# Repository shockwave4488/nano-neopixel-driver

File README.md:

# Nano NeoPixel driver
An all in one board for driving neopixel, or equivalent, led strips using an Arduino Nano

**WARNING: THIS BOARD IS 5V ONLY. APPLYING A HIGHER VOLTAGE WILL RESULT IN A DEAD ARDUINO AND LEDS**

Instructions for the jumpers on the back <br>
Adafruit recommends putting a 470 ohm resistor in series with the WS2812B data line. To acomodate both LED and GPIO signals, the back of the board has a resistor footprint and a solder jumper for each exposed DIO. Populate the resistor for DIO that will drive an LED signal, and solder the jumper for DIO that will be GPIO.

Assembly
1) Populatate the resistors and jumpers on the back as needed
2) Install the arduino
3) Attach wire or headers for Vin and the DIO
4) Install the capacitor

BOM <br>
1x Arduino Nano <br>
1x 1000uF Würth Elektronik 860010274015 (or comparable capacitor with same footprint) <br>
8x 470 ohm 0805 resistors <br>

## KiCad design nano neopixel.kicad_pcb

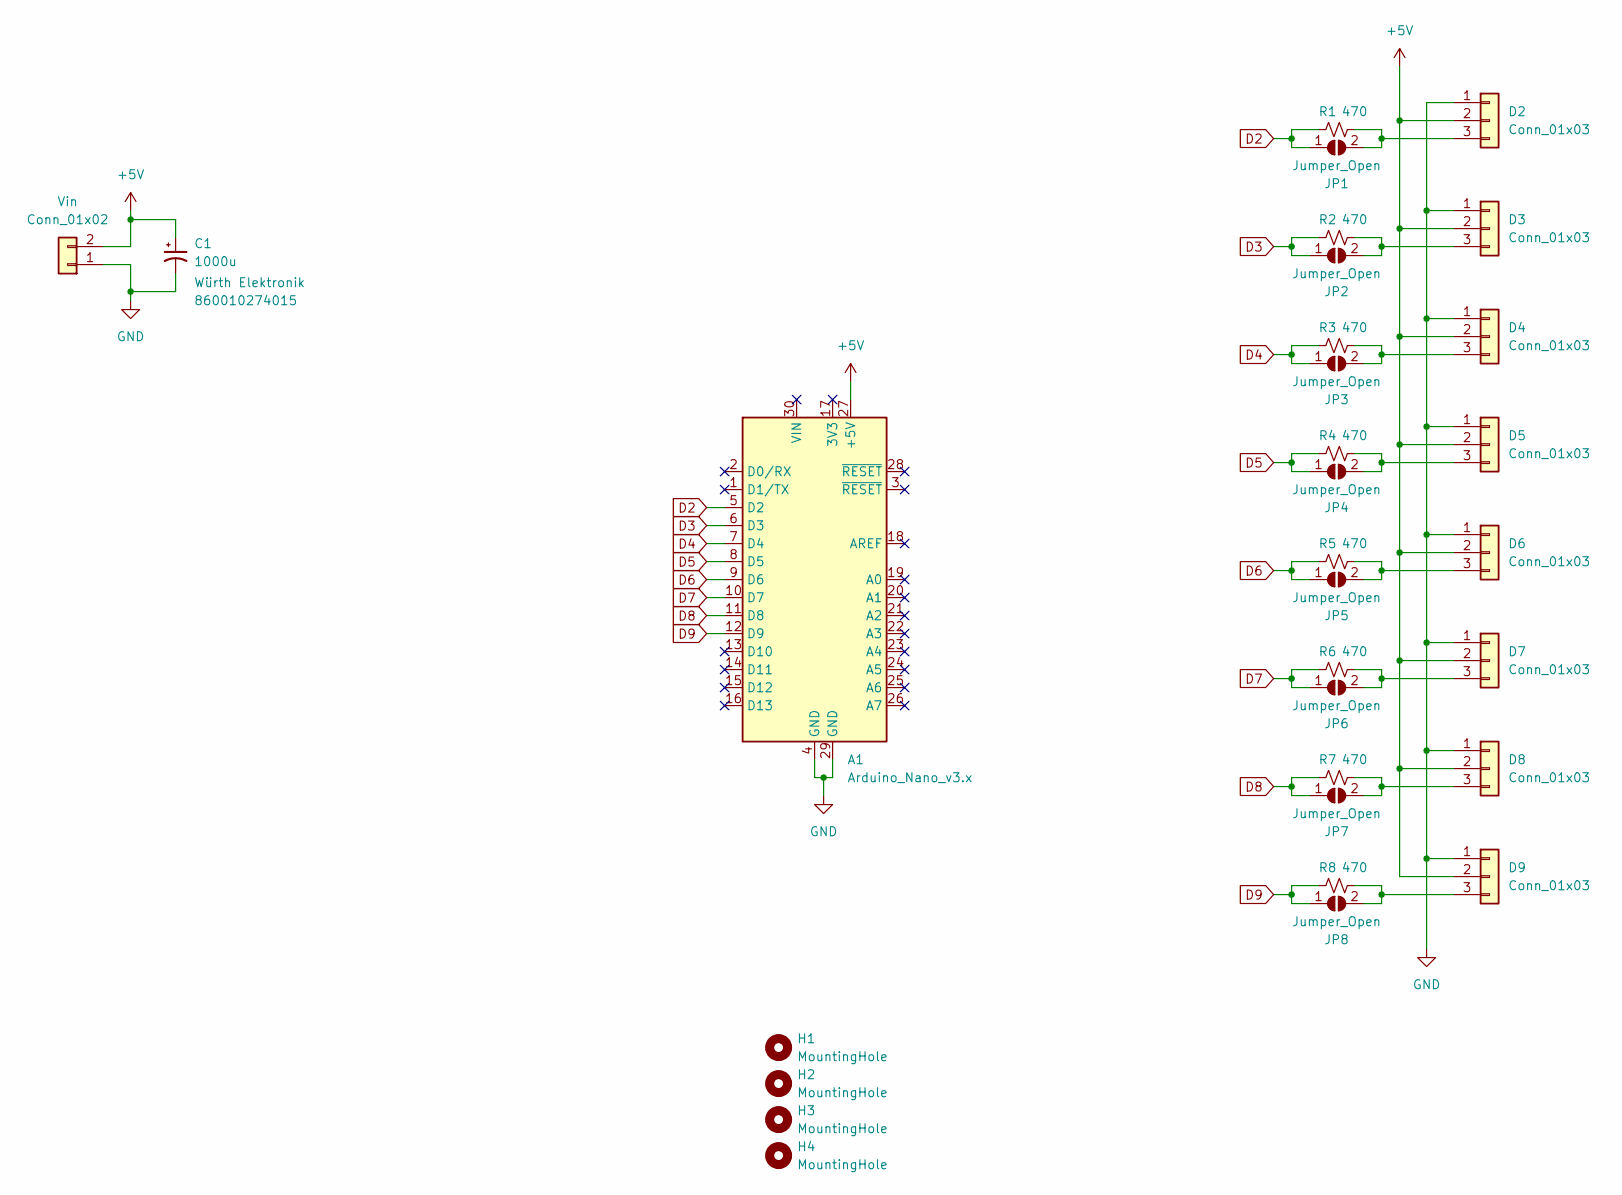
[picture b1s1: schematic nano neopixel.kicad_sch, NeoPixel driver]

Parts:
A1: Arduino_Nano_v3.x; Arduino_Nano
C1: 1000u; CP_Radial_D8.0mm_P3.50mm
D2, D3, D4, D5, D6, D7, D8, D9: Conn_01x03; PinHeader_1x03_P2.54mm_Vertical
H1, H2, H3, H4: MountingHole; MountingHole_3.2mm_M3
JP1, JP2, JP3, JP4, JP5, JP6, JP7, JP8: Jumper_Open; SolderJumper-2_P1.3mm_Open_Pad1.0x1.5mm
R1, R2, R3, R4, R5, R6, R7, R8: 470; R_0805_2012Metric
Vin: Conn_01x02; PinHeader_1x02_P2.54mm_Vertical

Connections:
+5V: A1.27 (+5V), C1.1, D2.2, D3.2, D4.2, D5.2, D6.2, D7.2, D8.2, D9.2, Vin.2
D2: A1.5 (D2), JP1.1 (A), R1.1
D3: A1.6 (D3), JP2.1 (A), R2.1
D4: A1.7 (D4), JP3.1 (A), R3.1
D5: A1.8 (D5), JP4.1 (A), R4.1
D6: A1.9 (D6), JP5.1 (A), R5.1
D7: A1.10 (D7), JP6.1 (A), R6.1
D8: A1.11 (D8), JP7.1 (A), R7.1
D9: A1.12 (D9), JP8.1 (A), R8.1
GND: A1.4 (GND), A1.29 (GND), C1.2, D2.1, D3.1, D4.1, D5.1, D6.1, D7.1, D8.1, D9.1, Vin.1
unnamed: D2.3, JP1.2 (B), R1.2
unnamed: D3.3, JP2.2 (B), R2.2
unnamed: D4.3, JP3.2 (B), R3.2
unnamed: D5.3, JP4.2 (B), R4.2
unnamed: D6.3, JP5.2 (B), R5.2
unnamed: D7.3, JP6.2 (B), R6.2
unnamed: D8.3, JP7.2 (B), R7.2
unnamed: D9.3, JP8.2 (B), R8.2

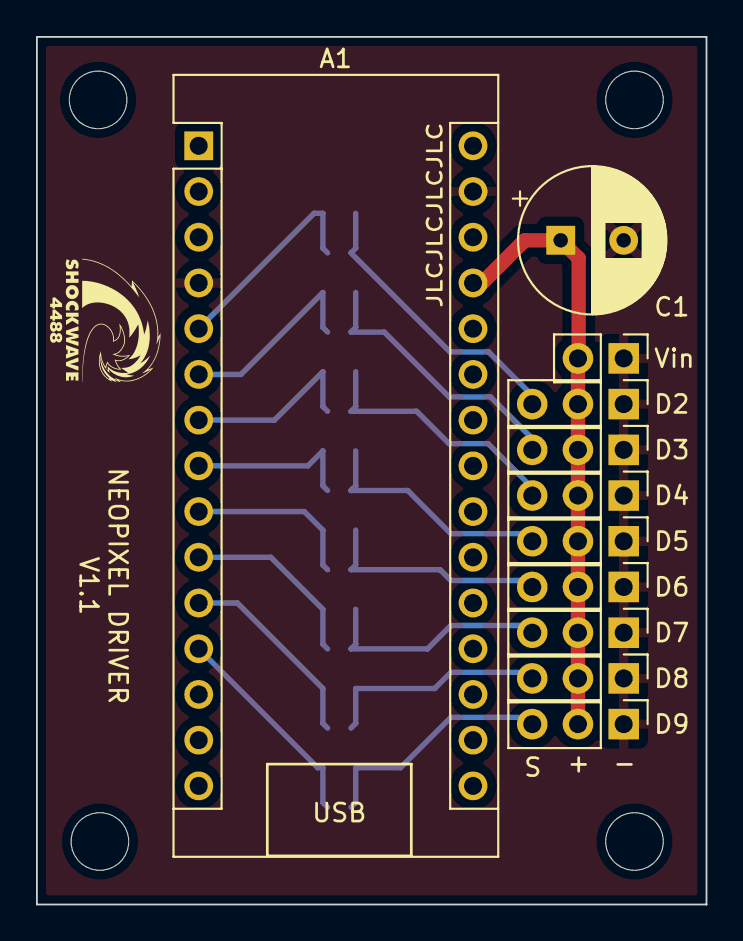
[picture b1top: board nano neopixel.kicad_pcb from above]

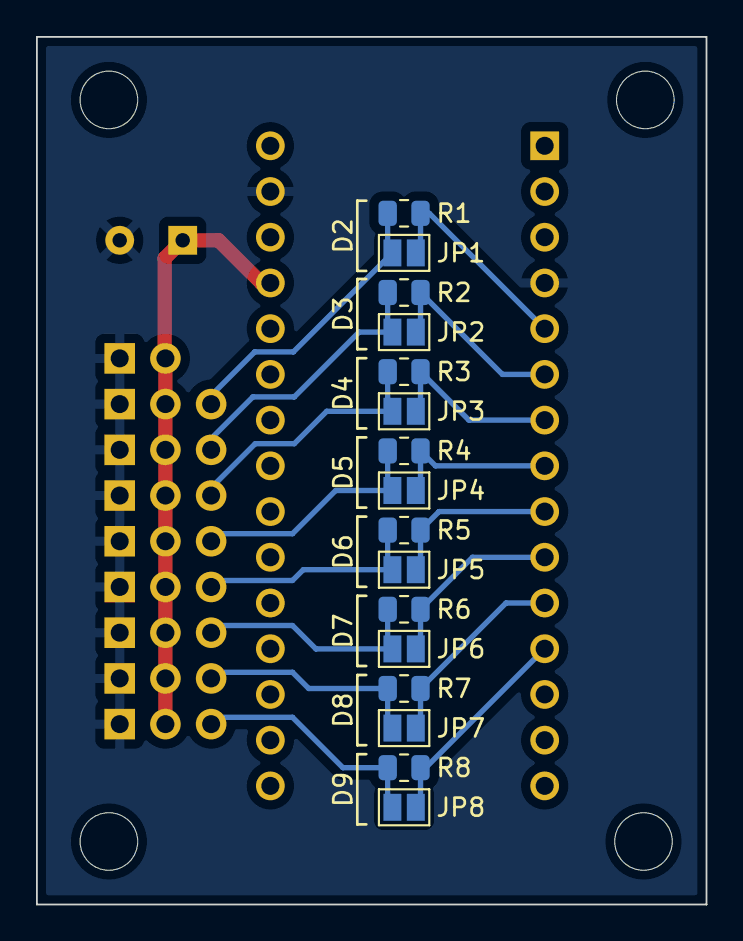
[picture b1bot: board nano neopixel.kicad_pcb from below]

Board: 2 copper layers, 37.2 x 48.2 mm, 31 parts (16 on the bottom side), 18 nets.

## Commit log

2022-10-21 completed layout
2022-10-21 added USB notation to the board
2022-10-21 Added instructions and bom
2022-10-21 attempting to make the warning bold
2022-10-21 Attempting to make the bom a list and make jumper instruction headder
2022-10-21 trying to make line breaks
2022-10-21 shifted the JLC order number designator away from the USB
